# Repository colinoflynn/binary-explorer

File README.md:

# Binary Explorer #

The Binary Explorer board is based on a previous Kickstarter project, and is designed to provide a useful platform for learning about digital logic. Compared to the previous version, the CPLD has been changed to an Altera MAX II which can be used with more recent design software (including on Windows 10). Note the old ("rev 02") version is completely incompatible with the current version, as the entire CPLD and programming interface has changed.

Binary Explorer includes:

- Altera MAX II CPLD which can be disabled to bypass outputs
- Breadboard for building logic circuits
- Switches, LEDs, and 7-segment displays
- Clocks for CPLD

The following is the old rev design, which looks almost identical from the top-side:

## Reference Designs / Examples ##

A number of templates/examples are provided for the Altera Quartus software. Always use these templates, as they contain considerable critical configuration regarding the device in use and board-specific setting (including pinouts and use of global disable).

If you fail to use these templates and things break, **we will laugh at you when they break**. 

## Using Breadboard ##

To use the breadboard, it's important to set the CPLD to "OFF". The "OFF" position should disable the I/O drivers on the CPLD, but it relies on the CPLD having been configured based on one of the template files.

If you do not set the CPLD to "OFF", or have programmed it with invalid code, you could find certain pins are being driven high/low against your will.

**NEVER use 5.0V on this board** - all I/O will only survive with 3.3V. The board does not include a 5.0V source to avoid this risk, but **DO NOT wire in an external 5.0V source**.

Be sure to **confirm any logic chips you are using** will operate at 3.3V OK.

## USB CPLD Programmer ##

The USB CPLD programming interface is provided thanks to work published at http://sa89a.net/mp.cgi/ele/ub.htm . This pushed the CPLD programming onto one of the lowest-cost USB interface chips which made this entire project possible.

We have adapted this design, with some very minor firmware changes to provide a slow and fast clock to the CPLD. This is often useful during development.

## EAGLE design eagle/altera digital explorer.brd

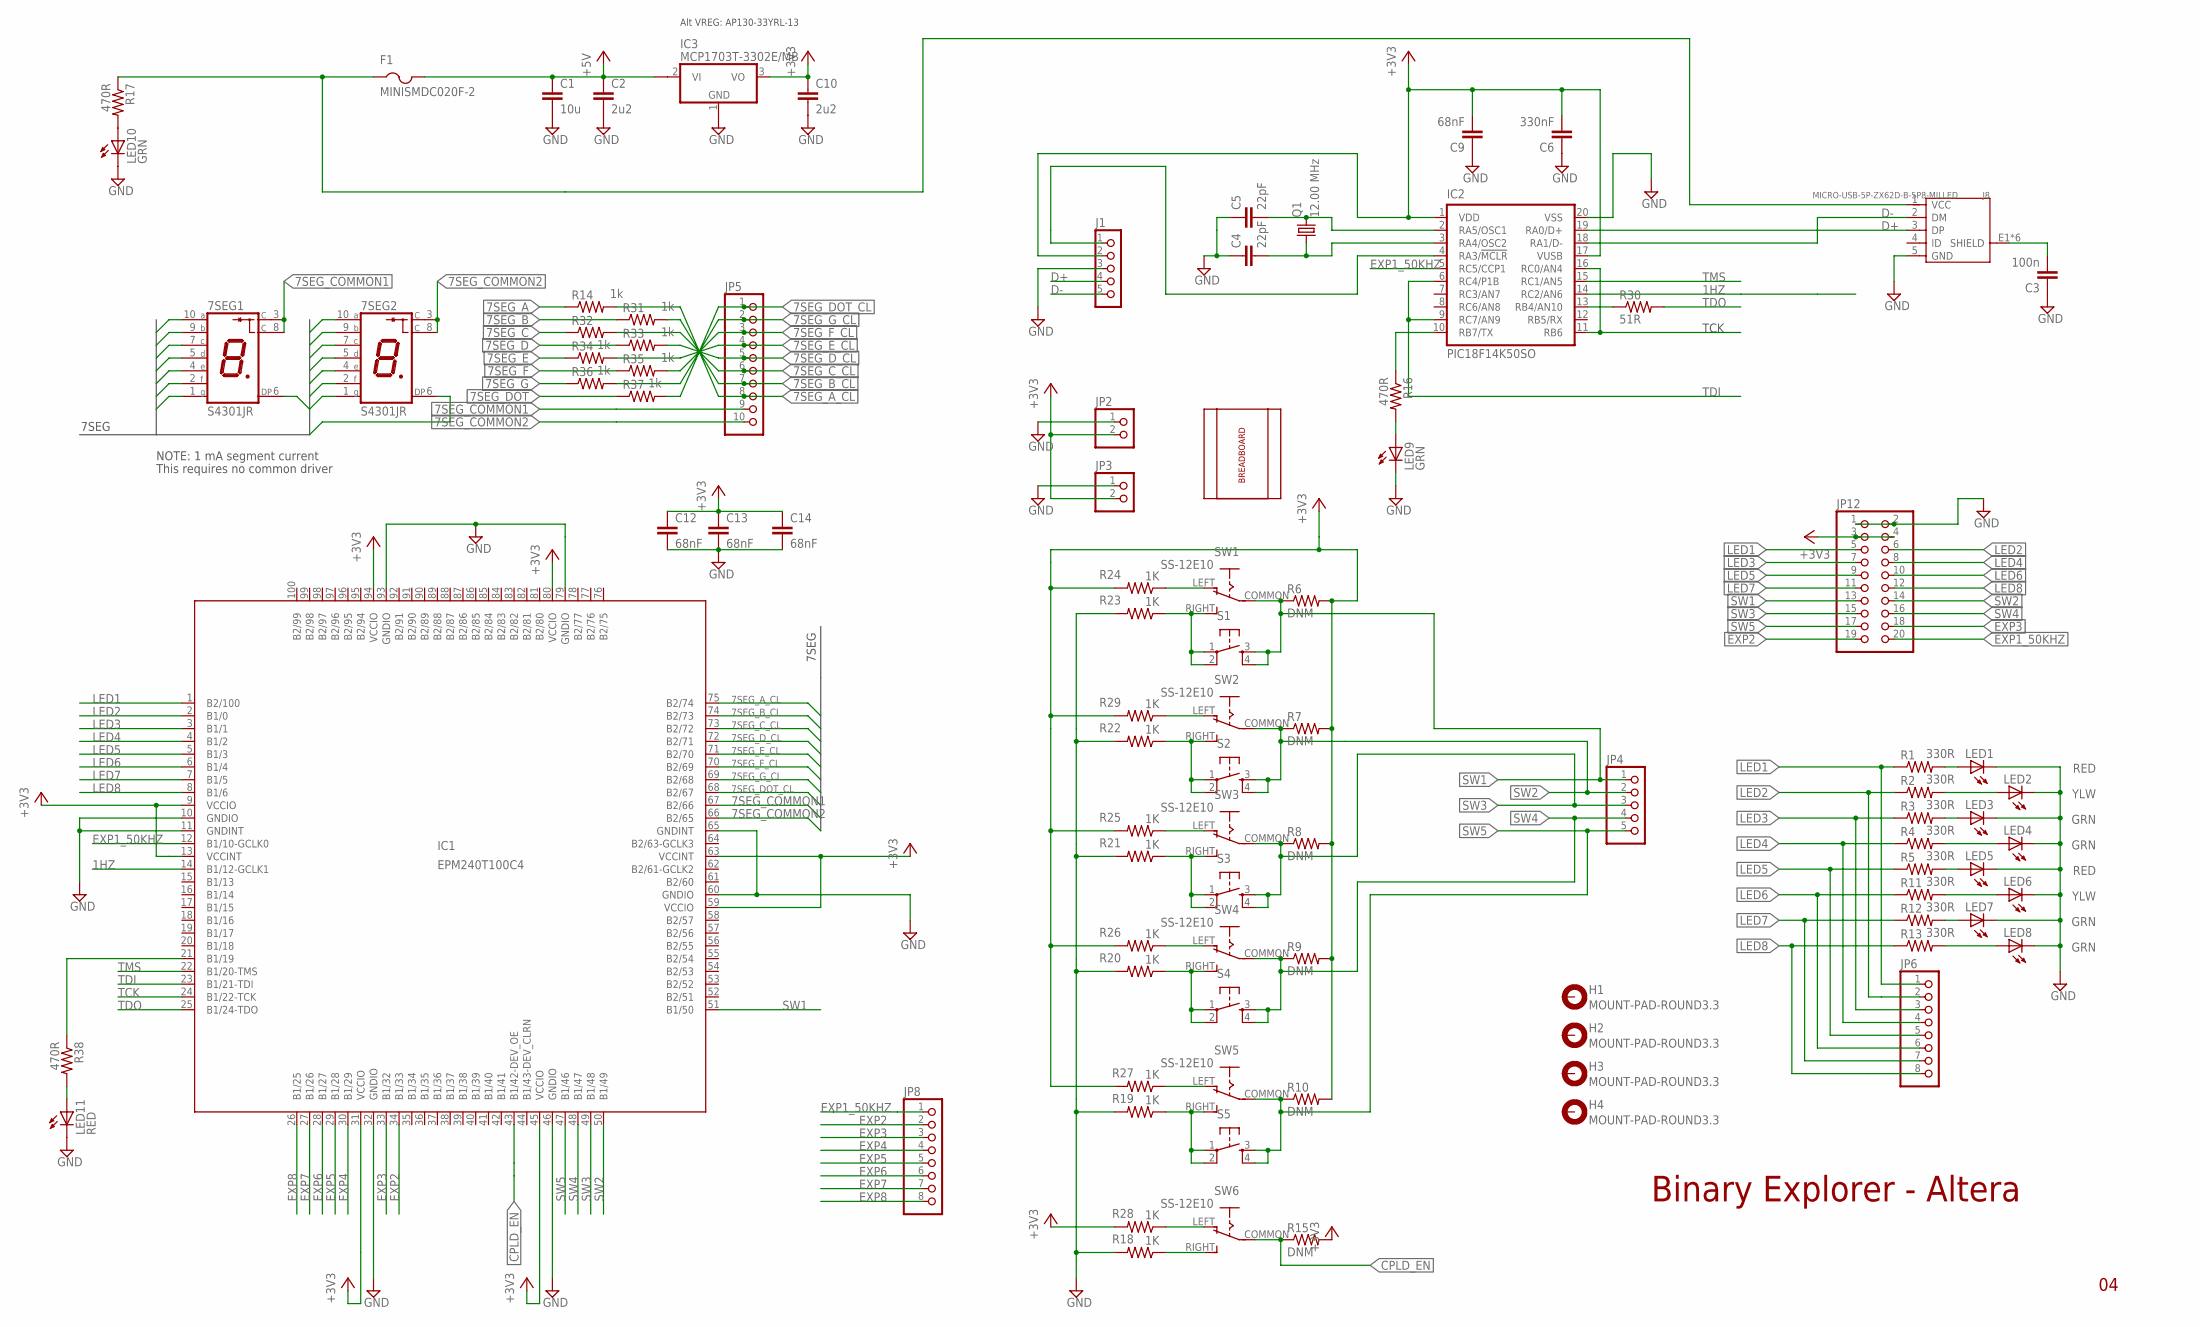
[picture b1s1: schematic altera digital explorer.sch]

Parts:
7SEG1, 7SEG2: S4301JR; S4301B
C1: 10u; C0805
C2, C10: 2u2; C0805
C3: 100n; C0603
C4, C5: 22pF; C0603
C6: 330nF; C0603
C9, C12, C14: 68nF; C0603
C13: 68nF; C0603K
F1: MINISMDC020F-2; 1812
H1, H2, H3, H4: MOUNT-PAD-ROUND3.3; 3,3-PAD
IC1: EPM240T100C4; TQFP100
IC2: PIC18F14K50SO; SO20
IC3: MCP1703T-3302E/MB; SOT89
J1: CON_HEADER_1X05-PTH; M1X5
J8: MICRO-USB-5P-ZX62D-B-5P8-MILLED; B-SMD-5P-TH-MILLED; MPN ZX62D-B-5P8
JP2, JP3: PINHD-1X2; 1X02
JP4: PINHD-1X5; 1X05
JP5: PINHD-1X10; 1X10
JP6, JP8: PINHD-1X8; 1X08
JP12: PINHD-2X10; 2X10
LED1, LED5, LED11: RED; CHIP-LED0805
LED2, LED6: YLW; CHIP-LED0805
LED3, LED4, LED7, LED8, LED9, LED10: GRN; CHIP-LED0805
Q1: 12.00 MHz; HC49UP; MPN ATS080BSM-1
R1, R2, R3, R4, R5, R11, R12, R13: 330R; R0603
R6, R7, R8, R9, R10, R15: DNM; R0603
R14, R31, R33, R34, R35, R36, R37: 1k; R0603
R16, R17, R38: 470R; R0603
R18, R19, R20, R21, R22, R23, R24, R25, R26, R27, R28, R29: 1K; R0603
R30: 51R; R0603
R32: R-US_R0603; R0603
S1, S2, S3, S4, S5: TAC_SWITCHPTH; TACTILE-PTH
SW1, SW2, SW3, SW4, SW5, SW6: SS-12E10
U$1: BB-400TP

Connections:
1HZ: IC1.14 (B1/12-GCLK1), IC2.14 (RC2/AN6)
7SEG_A: 7SEG1.10 (A), 7SEG2.10 (A), R14.1
7SEG_A_CL: IC1.75 (B2/74), JP5.8, R14.2
7SEG_B: 7SEG1.9 (B), 7SEG2.9 (B), R31.1
7SEG_B_CL: IC1.74 (B2/73), JP5.7, R31.2
7SEG_C: 7SEG1.7 (C), 7SEG2.7 (C), R32.1
7SEG_COMMON1: 7SEG1.3 (C), 7SEG1.8 (C), IC1.67 (B2/66), JP5.9
7SEG_COMMON2: 7SEG2.3 (C), 7SEG2.8 (C), IC1.66 (B2/65), JP5.10
7SEG_C_CL: IC1.73 (B2/72), JP5.6, R32.2
7SEG_D: 7SEG1.5 (D), 7SEG2.5 (D), R33.1
7SEG_DOT: 7SEG1.6 (DP), 7SEG2.6 (DP), R37.1
7SEG_DOT_CL: IC1.68 (B2/67), JP5.1, R37.2
7SEG_D_CL: IC1.72 (B2/71), JP5.5, R33.2
7SEG_E: 7SEG1.4 (E), 7SEG2.4 (E), R34.1
7SEG_E_CL: IC1.71 (B2/70), JP5.4, R34.2
7SEG_F: 7SEG1.2 (F), 7SEG2.2 (F), R35.1
7SEG_F_CL: IC1.70 (B2/69), JP5.3, R35.2
7SEG_G: 7SEG1.1 (G), 7SEG2.1 (G), R36.1
7SEG_G_CL: IC1.69 (B2/68), JP5.2, R36.2
+3V3: C6.2, C9.2, C10.1, C12.1, C13.1, C14.1, IC1.9 (VCCIO), IC1.13 (VCCINT), IC1.31 (VCCIO), IC1.45 (VCCIO), IC1.59 (VCCIO), IC1.63 (VCCINT), IC1.80 (VCCIO), IC1.94 (VCCIO), IC2.1 (VDD), IC2.17 (VUSB), IC3.3 (VO), J1.2, JP2.2, JP3.2, JP12.3, JP12.4, R6.2, R7.2, R8.2, R9.2, R10.2, R15.2, R24.2, R25.2, R26.2, R27.2, R28.2, R29.2
+5V: C1.1, C2.1, F1.2, IC3.2@1 (VI1)
CPLD_EN: IC1.43 (B1/42-DEV_OE), R15.1, SW6.COMMON
D+: IC2.19 (RA0/D+), J1.4, J8.3 (DP)
D-: IC2.18 (RA1/D-), J1.5, J8.2 (DM)
EXP1_50KHZ: IC1.12 (B1/10-GCLK0), IC2.5 (RC5/CCP1), JP8.1, JP12.20
EXP2: IC1.34 (B1/33), JP8.2, JP12.19
EXP3: IC1.33 (B1/32), JP8.3, JP12.18
EXP4: IC1.30 (B1/29), JP8.4
EXP5: IC1.29 (B1/28), JP8.5
EXP6: IC1.28 (B1/27), JP8.6
EXP7: IC1.27 (B1/26), JP8.7
EXP8: IC1.26 (B1/25), JP8.8
GND: C1.2, C2.2, C3.1, C4.1, C5.1, C6.1, C9.1, C10.2, C12.2, C13.2, C14.2, IC1.10 (GNDIO), IC1.11 (GNDINT), IC1.32 (GNDIO), IC1.46 (GNDIO), IC1.60 (GNDIO), IC1.65 (GNDINT), IC1.79 (GNDIO), IC1.93 (GNDIO), IC2.20 (VSS), IC3.1 (GND), J1.3, J8.5 (GND), JP2.1, JP3.1, JP12.1, JP12.2, LED1.C, LED2.C, LED3.C, LED4.C, LED5.C, LED6.C, LED7.C, LED8.C, LED9.C, LED10.C, LED11.C, R18.2, R19.2, R20.2, R21.2, R22.2, R23.2
LED1: IC1.1 (B2/100), JP6.1, JP12.5, R1.1
LED2: IC1.2 (B1/0), JP6.2, JP12.6, R2.1
LED3: IC1.3 (B1/1), JP6.3, JP12.7, R3.1
LED4: IC1.4 (B1/2), JP6.4, JP12.8, R4.1
LED5: IC1.5 (B1/3), JP6.5, JP12.9, R5.1
LED6: IC1.6 (B1/4), JP6.6, JP12.10, R11.1
LED7: IC1.7 (B1/5), JP6.7, JP12.11, R12.1
LED8: IC1.8 (B1/6), JP6.8, JP12.12, R13.1
unnamed: IC2.10 (RB7/TX), R16.1
unnamed: LED4.A, R4.2
unnamed: IC2.13 (RB4/AN10), R30.1
unnamed: IC1.21 (B1/19), R38.1
unnamed: R22.1, S2.1, S2.2, SW2.RIGHT (S)
unnamed: F1.1, J8.1 (VCC), R17.1
unnamed: C3.2, J8.E1 (SHIELD), J8.E2 (SHIELD), J8.P$1 (SHIELD), J8.P$2 (SHIELD), J8.P$3 (SHIELD), J8.P$4 (SHIELD)
unnamed: LED11.A, R38.2
unnamed: IC2.4 (RA3/!MCLR!), J1.1
unnamed: LED9.A, R16.2
unnamed: C5.2, IC2.2 (RA5/OSC1), Q1.2
unnamed: C4.2, IC2.3 (RA4/OSC2), Q1.1
unnamed: R20.1, S4.1, S4.2, SW4.RIGHT (S)
unnamed: LED10.A, R17.2
unnamed: R21.1, S3.1, S3.2, SW3.RIGHT (S)
unnamed: R18.1, SW6.RIGHT (S)
unnamed: R19.1, S5.1, S5.2, SW5.RIGHT (S)
unnamed: LED1.A, R1.2
unnamed: R23.1, S1.1, S1.2, SW1.RIGHT (S)
unnamed: LED2.A, R2.2
unnamed: LED3.A, R3.2
unnamed: LED5.A, R5.2
unnamed: LED6.A, R11.2
unnamed: LED7.A, R12.2
unnamed: LED8.A, R13.2
unnamed: R24.1, SW1.LEFT (O)
unnamed: R25.1, SW3.LEFT (O)
unnamed: R26.1, SW4.LEFT (O)
unnamed: R27.1, SW5.LEFT (O)
unnamed: R28.1, SW6.LEFT (O)
unnamed: R29.1, SW2.LEFT (O)
SW1: IC1.51 (B1/50), JP4.1, JP12.13, R6.1, S1.3, S1.4, SW1.COMMON
SW2: IC1.50 (B1/49), JP4.2, JP12.14, R7.1, S2.3, S2.4, SW2.COMMON
SW3: IC1.49 (B1/48), JP4.3, JP12.15, R8.1, S3.3, S3.4, SW3.COMMON
SW4: IC1.48 (B1/47), JP4.4, JP12.16, R9.1, S4.3, S4.4, SW4.COMMON
SW5: IC1.47 (B1/46), JP4.5, JP12.17, R10.1, S5.3, S5.4, SW5.COMMON
TCK: IC1.24 (B1/22-TCK), IC2.11 (RB6), IC2.16 (RC0/AN4)
TDI: IC1.23 (B1/21-TDI), IC2.6 (RC4/P1B), IC2.9 (RC7/AN9)
TDO: IC1.25 (B1/24-TDO), R30.2
TMS: IC1.22 (B1/20-TMS), IC2.15 (RC1/AN5)

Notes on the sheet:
7SEG
Alt VREG: AP130-33YRL-13
TCK
NOTE: 1 mA segment current
This requires no common driver
Binary Explorer - Altera

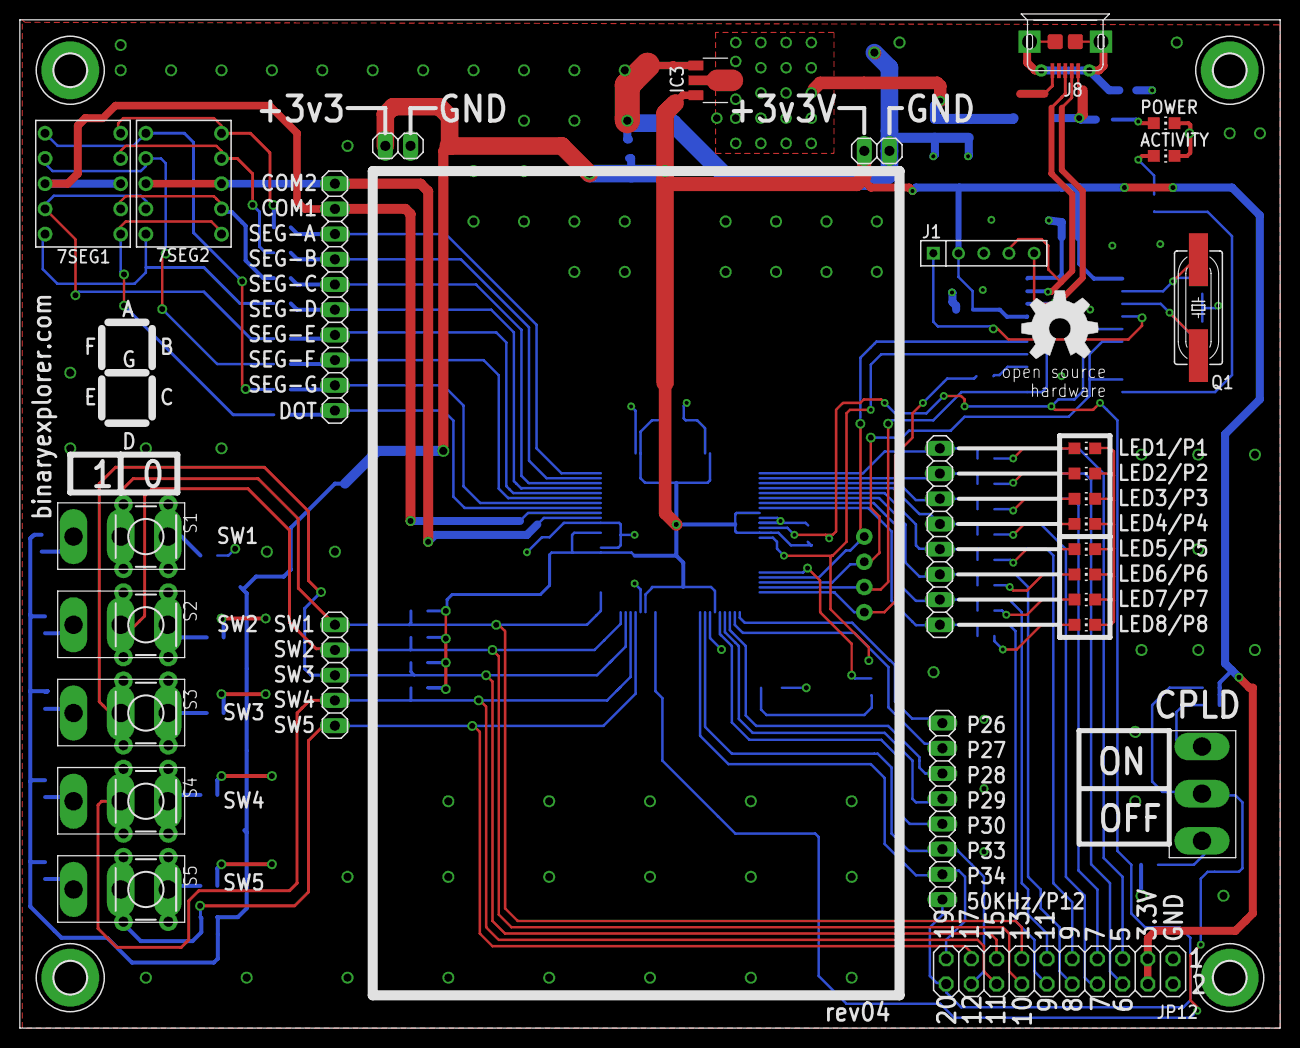
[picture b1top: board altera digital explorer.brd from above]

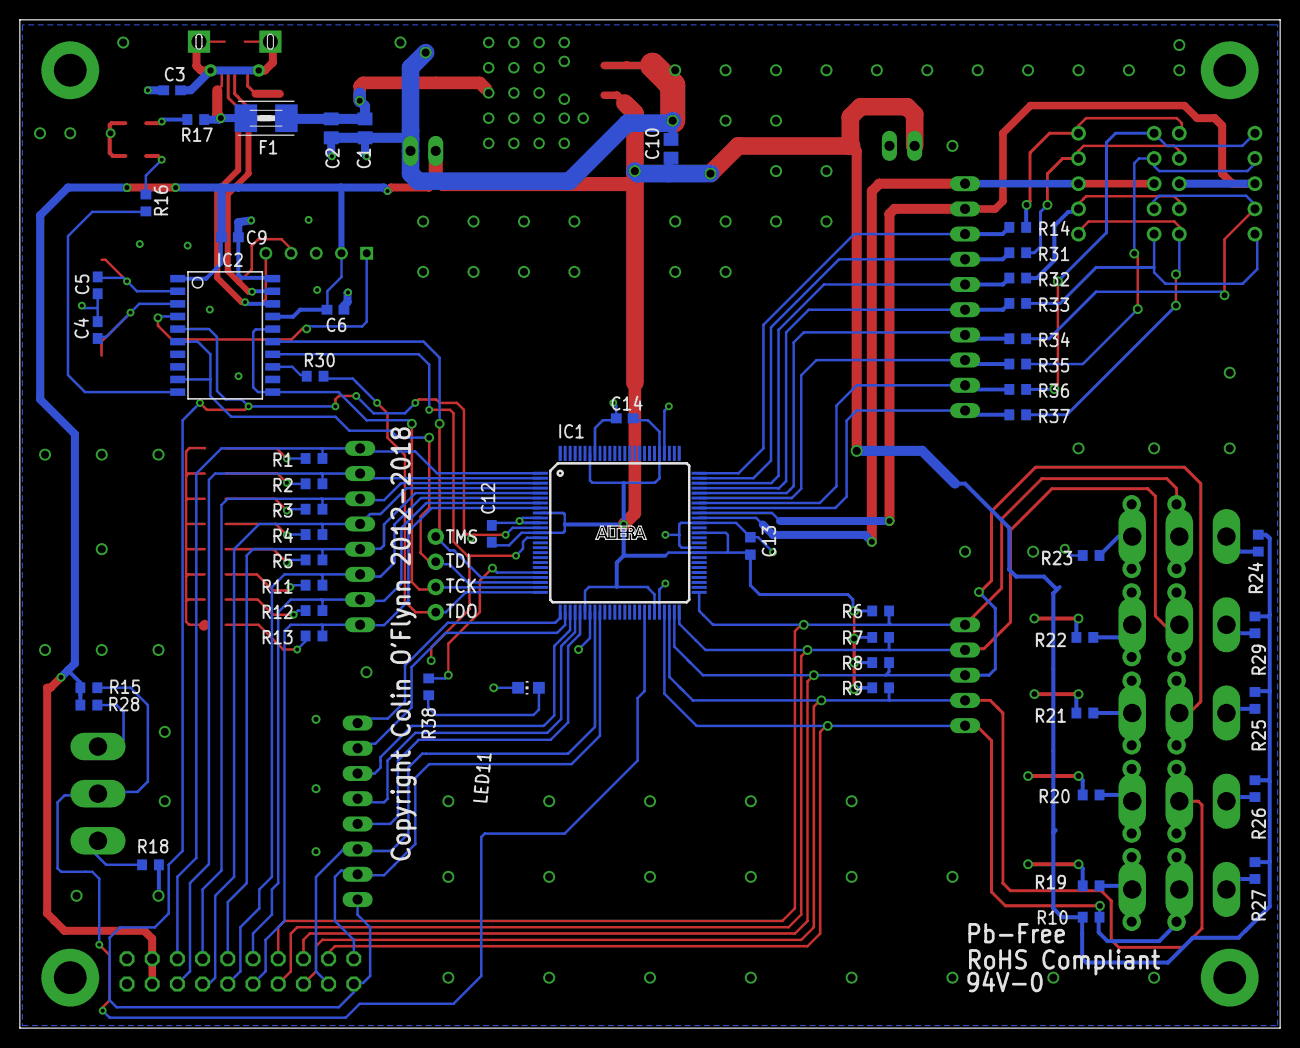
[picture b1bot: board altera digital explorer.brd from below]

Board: 2 copper layers, 126.9 x 101.5 mm, 93 parts (53 on the bottom side), 81 nets.

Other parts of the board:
U$2: OSHW_8MM

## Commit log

2018-06-26 Initial addition of materials
2018-06-26 Updates - make schematic nicer, make PDF
2018-07-04 Add new MPLAB X project
2018-07-04 PCB update: fix incorrect routing of JTAG programming outputs, change lighthouse to be CPLD controlled, add pushbuttons in addition to switch
2018-07-05 FW: Fix clock outputs so they work (closes #3)
2018-07-05 Fix bad pin numbering (closes #1) other minor additions
2018-07-05 Add gerber snapshots
2018-07-05 Add gitigore, add gerber move script
2018-07-05 Fix net name for 32khz-->50khz, update schematic print
2018-07-12 Small fixes to schematic
2018-07-12 Continuing clean-up of schematic + pcb. Add hex-file for microchip with the clock outputs all turned on.

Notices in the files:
eagle/altera digital explorer.brd:
Copyright Colin O'Flynn 2012-2018
parts and their libraries:
SparkFun: Licensing: CC v3.0 Share-Alike You are welcome to use this library for commercial purposes.
